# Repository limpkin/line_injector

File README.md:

# line_injector
a 60V/5A 50MHz line injector

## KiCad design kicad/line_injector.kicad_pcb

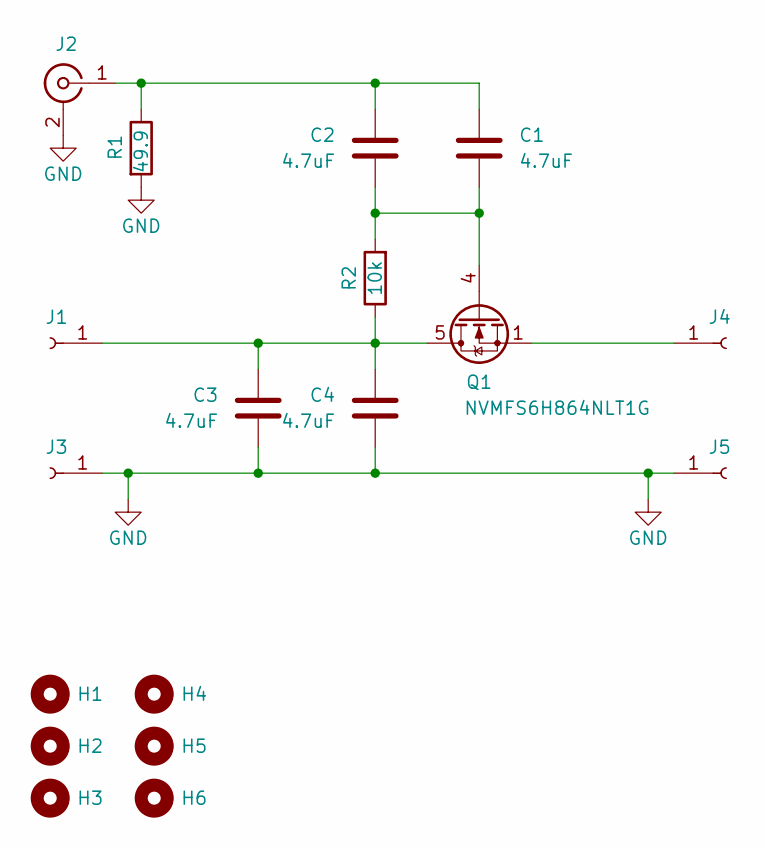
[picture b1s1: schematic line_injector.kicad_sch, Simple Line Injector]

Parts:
C1, C2, C3, C4: 4.7uF; C_1210_3225Metric
H1, H2, H3, H4, H5, H6: MountingHole; MountingHole_3.2mm_M3_ISO7380_Pad
J1, J3, J4, J5: Conn_01x01_Socket; BANANA_ALIEXPRESS
J2: Conn_Coaxial; SMA_ALIEXPRESS
Q1: NVMFS6H864NLT1G
R1: 49.9; R_0805_2012Metric
R2: 10k; R_0805_2012Metric

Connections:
GND: C3.2, C4.2, J2.2 (Ext), J3.1, J5.1, R1.2
unnamed: C3.1, C4.1, J1.1, Q1.5 (D), R2.1
unnamed: C1.1, C2.1, J2.1 (In), R1.1
unnamed: J4.1, Q1.1 (S), Q1.2 (S), Q1.3 (S)
unnamed: C1.2, C2.2, Q1.4 (G), R2.2

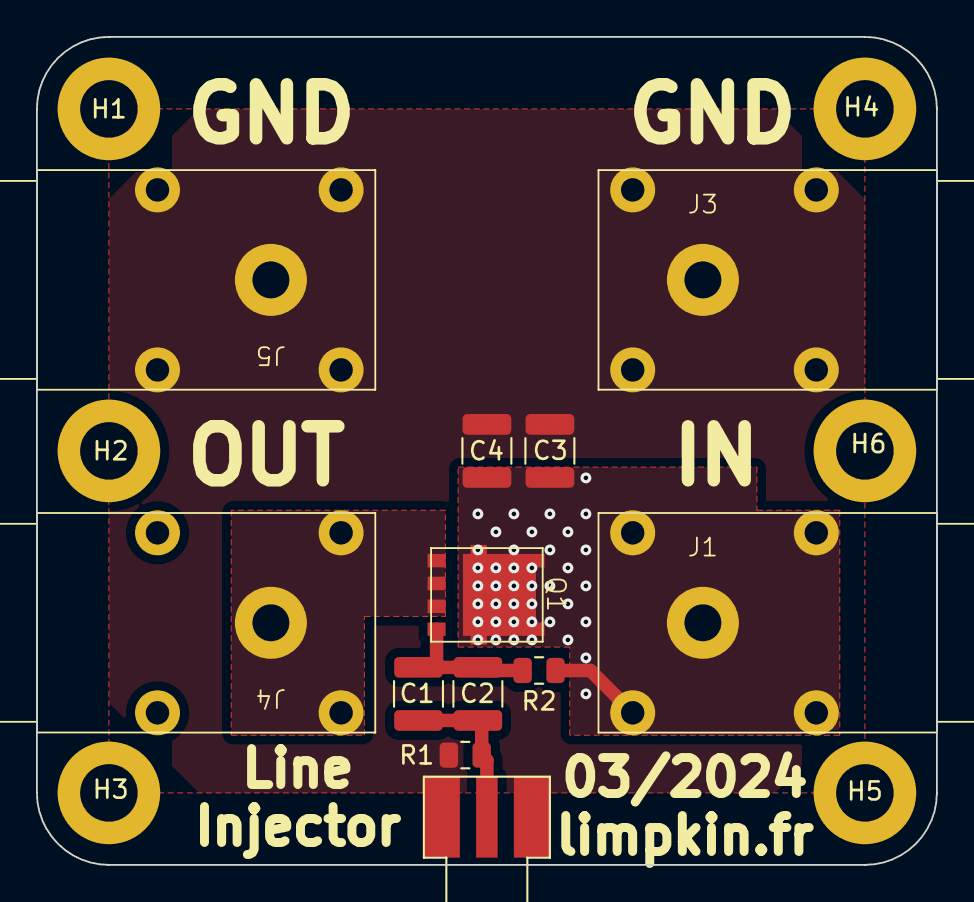
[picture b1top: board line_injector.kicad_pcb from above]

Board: 2 copper layers, 50.0 x 46.0 mm, 18 parts (0 on the bottom side), 5 nets.

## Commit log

2024-03-25 full commit
